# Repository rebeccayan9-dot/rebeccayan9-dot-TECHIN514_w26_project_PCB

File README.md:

# rebeccayan9-dot-TECHIN514_w26_project_PCB

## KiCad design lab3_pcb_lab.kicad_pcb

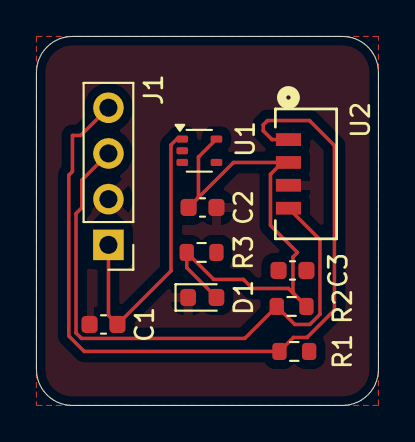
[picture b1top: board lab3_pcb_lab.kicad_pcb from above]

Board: 2 copper layers, 19.0 x 20.5 mm, 10 parts (0 on the bottom side), 5 nets.

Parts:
C1, C2, C3: C; C_0603_1608Metric
D1: LED; LED_0603_1608Metric
J1: Conn_01x04_Pin; PinHeader_1x04_P2.54mm_Vertical
R1, R2: 4.7k; R_0603_1608Metric
R3: 330; R_0603_1608Metric
U1: MIC5376-2.8YC5-TR; SOT-353_SC-70-5
U2: SMT_L7700-TT; VEML7700-TR

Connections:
+2V8: C2.1, C3.1, D1.2 (A), R1.2, R2.2, R3.1, U1.5 (VOUT), U2.2
/SCL: J1.4, R1.1, U2.1
/SDA: J1.3, R2.1, U2.4
/VIN: C1.2, J1.1, U1.1 (VIN)
GND: C1.1, C2.2, C3.2, D1.1 (K), J1.2, U1.2 (GND), U2.3

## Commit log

2026-01-30 add pdf
2026-01-30 organize
